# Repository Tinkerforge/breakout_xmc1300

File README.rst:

XMC1300 Breakout
================

This repository contains the firmware source code and the hardware design
files. The documentation generator configs can be found at
https://github.com/Tinkerforge/generators

Repository Content
------------------

software/:
 * examples/: Examples for all supported languages
 * build/: Makefile and compiled files
 * src/: Source code of firmware
 * generate_makefile: Shell script to generate Makefile from cmake script

hardware/:
 * Contains kicad project files and additionally schematics as pdf

datasheets/:
 * Contains datasheets for sensors and complex ICs that are used

Hardware
--------

The hardware is designed with the open source EDA Suite KiCad
(http://www.kicad.org). Before you are able to open the files,
you have to install the Tinkerforge kicad-libraries
(https://github.com/Tinkerforge/kicad-libraries). You can either clone
them directly in hardware/ or clone them in a separate folder and
symlink them into hardware/
(ln -s kicad_path/kicad-libraries project_path/hardware). After that you
can open the .pro file in hardware/ with kicad and from there view and
modify the schematics and the PCB layout.

Software
--------

To compile the c code we recommend you to install the newest CodeSourcery arm
eabi gcc compiler
(http://www.codesourcery.com/sgpp/lite/arm/portal/subscription?@template=lite).
You also need to install bricklib (https://github.com/Tinkerforge/bricklib)
and brickletlib (https://github.com/Tinkerforge/brickletlib).
You can either clone them directly in software/src/ or clone them in a
separate folder and symlink them into software/src/
(ln -s bricklib_path/bricklib project_path/software/src/).

After that you can generate a Makefile from the cmake script with the
generate_makefile shell script (in software/) and build the firmware
by invoking make in software/build/. The firmware (.bin) can then be found
in software/build/ and uploaded with brickv (click button "Flashing"
on start screen).

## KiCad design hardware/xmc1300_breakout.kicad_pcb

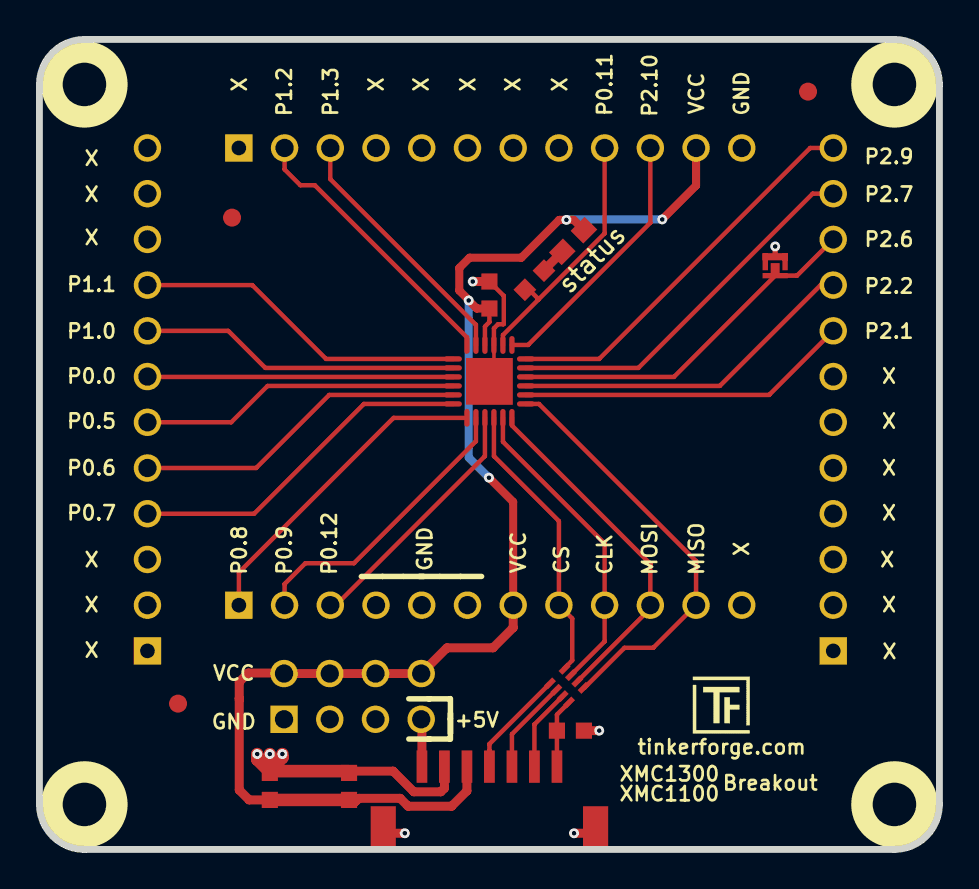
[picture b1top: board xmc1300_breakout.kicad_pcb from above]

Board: 2 copper layers, 50.0 x 45.0 mm, 24 parts (0 on the bottom side), 30 nets.

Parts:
C1: 10uF; C0603F
C2: 1uF; C0603F
C3: 220pF; C0603F
C4: 100nF; C0603F
D3: blue; D0603E
Fiducial_Mark: VAL**; Fiducial_Mark
Fiducial_Mark#2, Fiducial_Mark#3: VAL**; Fiducial_Mark
P1: CON-SENSOR2
P2: BOOT; SolderJumper
P3, P4, P5, P6: CONN_01X12; pin_array_12
P7: CONN_02X04; pin_array_4x2
R1: 1k; R0603F
RP1: 82; 4X0402
U1: XMC1XXX24; QFN24-4x4mm-0.5mm
U2, U3, U4, U5: DRILL; DRILL_NP
VAL: CE_5mm
VAL#2: WEEE_7mm_back

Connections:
+5V: P1.1, P7.7
GND: C1.1, C2.1, C3.1, C4.2, P1.2, P1.EP, P2.1, P3.12, P5.5, P5.6, P7.1, P7.3, P7.5, U1.9, U1.EXP
unnamed: C3.2, P1.7, RP1.8
unnamed: D3.2, R1.2
unnamed: P1.4, RP1.5
unnamed: P1.5, RP1.6
unnamed: P1.6, RP1.7
Pin4: P4.9, U1.13
Pin5: P4.8, U1.14
Pin6: P4.7, U1.15
Pin7: P4.6, U1.16
Pin8: P4.5, U1.17
Pin9: P4.4, U1.18
Pin13: P5.1, U1.19
Pin14: P5.2, U1.20
Pin15: P5.3, U1.21
Pin32: P6.8, U1.2
Pin33: P6.9, U1.3
Pin34: P2.2, P6.10, U1.4
Pin35: P6.11, U1.5
Pin36: P6.12, U1.6
Pin39: P3.10, U1.7
Pin40: P3.9, R1.1, U1.8
Pin46: P3.3, U1.11
Pin47: P3.2, U1.12
S-CLK: P5.9, RP1.3, U1.23
S-CS: P5.8, RP1.4, U1.22
S-MISO: P5.11, RP1.1, U1.1
S-MOSI: P5.10, RP1.2, U1.24
VCC: C1.2, C2.2, C4.1, D3.1, P1.3, P3.11, P5.7, P7.2, P7.4, P7.6, P7.8, U1.10

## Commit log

2017-09-13 Add schematic
2017-09-13 Add PCB
2017-09-14 Fix BootPad & add status marking for status LED
2017-09-18 Fix GND path under MCU
2017-10-13 Add initial stub implementation
2018-03-05 Remove unused flash-size define
2021-10-25 Update KiCad link
    https://www.kicad.org/blog/2021/10/Avoid-links-to-former-kicad-domain/

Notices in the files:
hardware/xmc1300_breakout.kicad_pcb:
Licensed under CERN OHL v.1.1
Copyright (©) 2017, B.Nordmeyer
Copyright Tinkerforge GmbH 2015.
This documentation describes Open Hardware and is licensed under the
CERN OHL v. 1.1.
